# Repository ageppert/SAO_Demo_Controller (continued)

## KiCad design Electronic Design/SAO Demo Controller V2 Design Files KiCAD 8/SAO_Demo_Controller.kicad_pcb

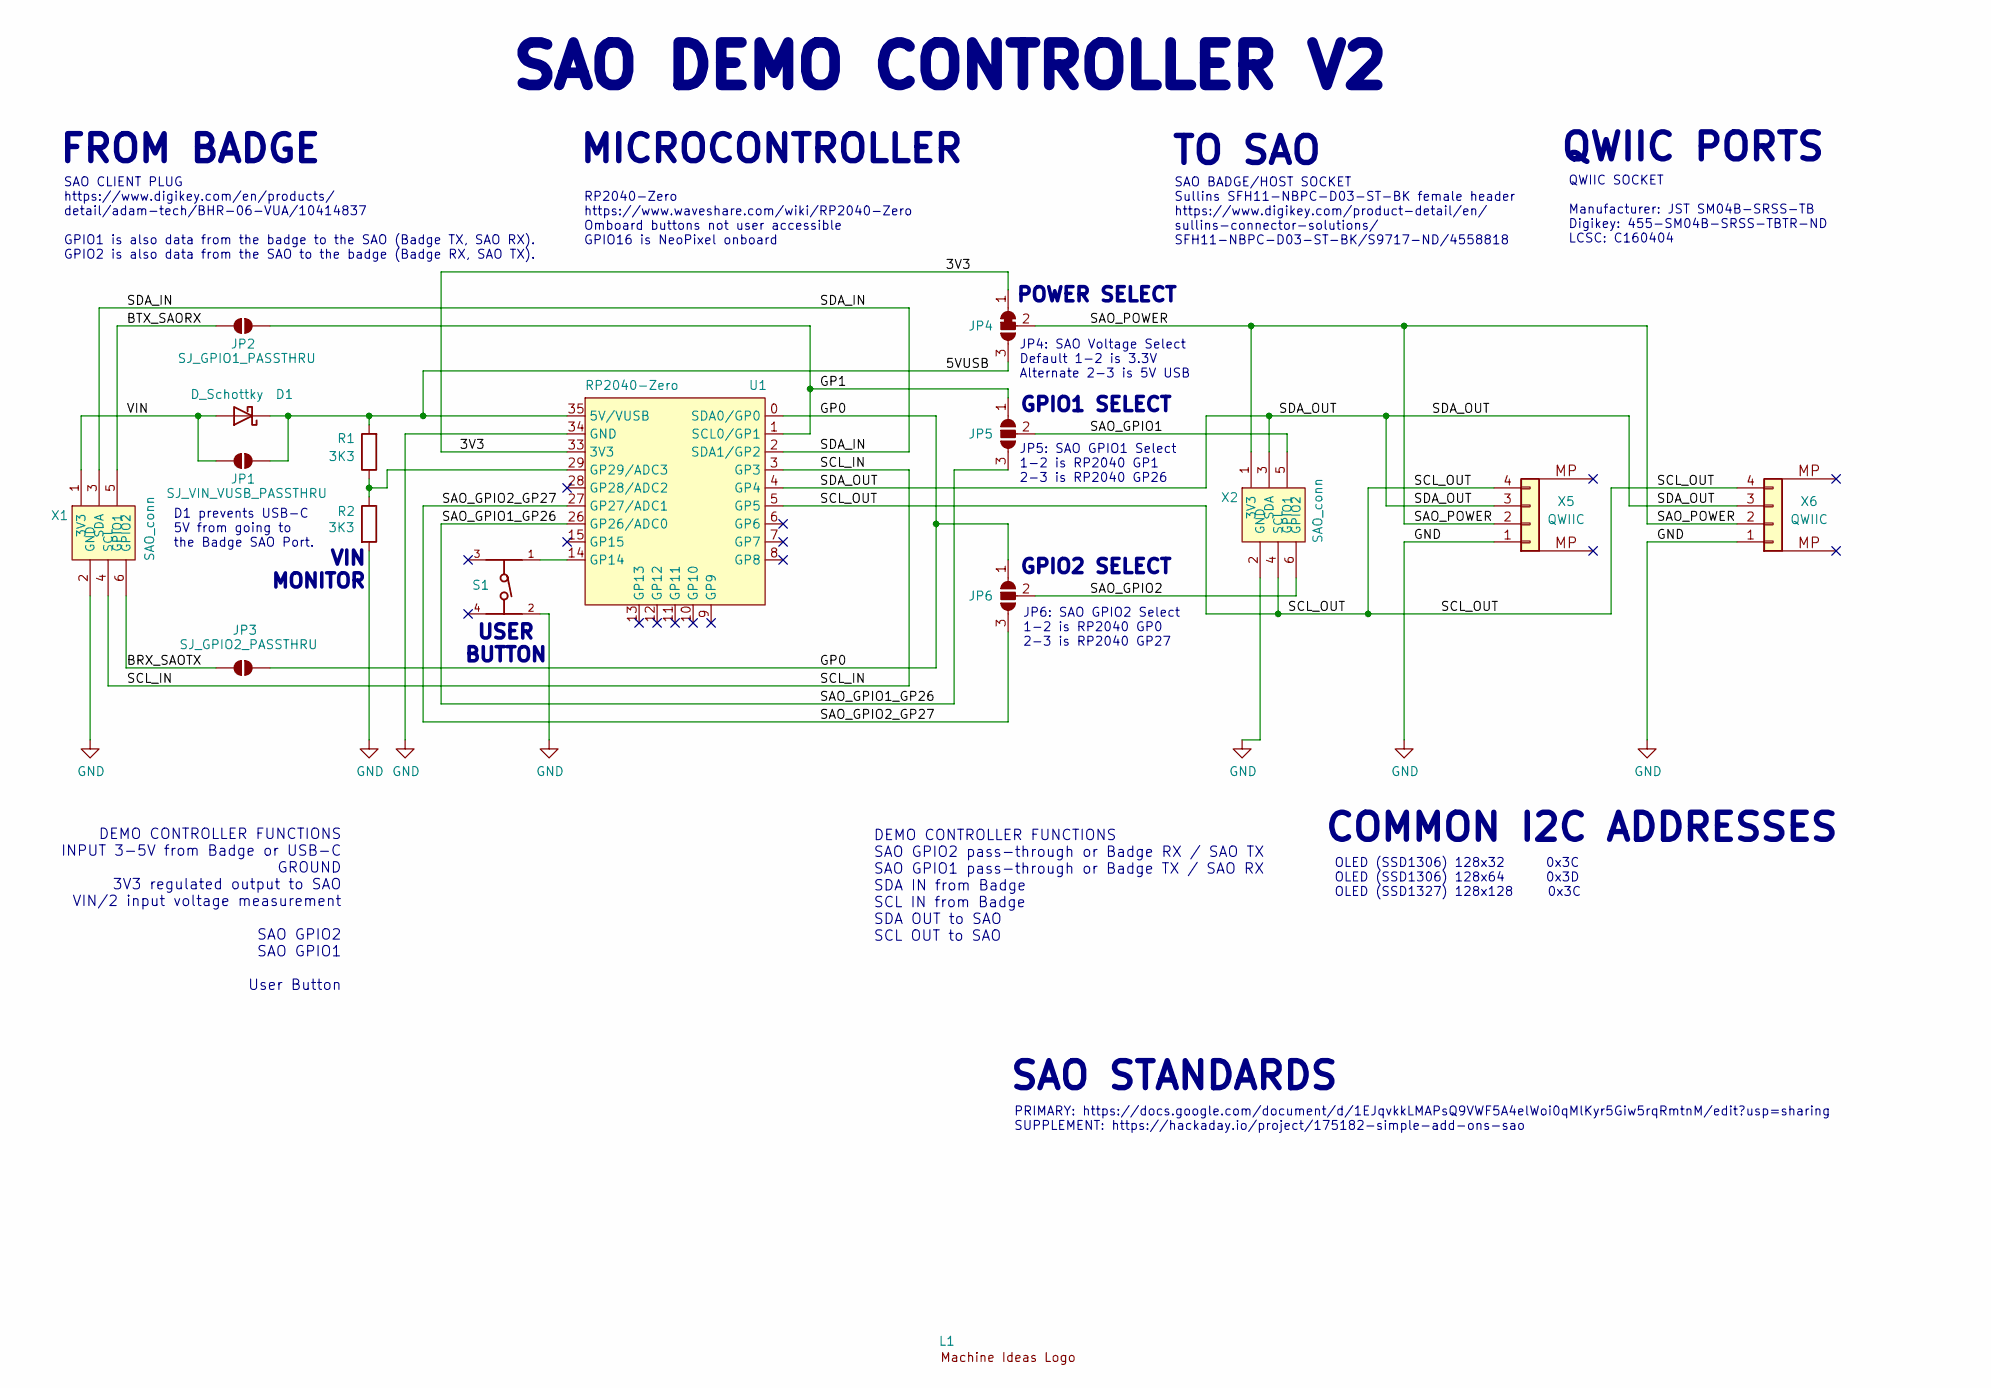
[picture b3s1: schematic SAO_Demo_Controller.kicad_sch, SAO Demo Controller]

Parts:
D1: D_Schottky; D_0805_2012Metric
JP1: SJ_VIN_VUSB_PASSTHRU; SolderJumper-2_P1.3mm_Open_RoundedPad1.0x1.5mm
JP2: SJ_GPIO1_PASSTHRU; SolderJumper-2_P1.3mm_Open_RoundedPad1.0x1.5mm
JP3: SJ_GPIO2_PASSTHRU; SolderJumper-2_P1.3mm_Open_RoundedPad1.0x1.5mm
JP4: SolderJumper_3_Open; SolderJumper-3_P1.3mm_Bridged12_RoundedPad1.0x1.5mm_NumberL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
JP5, JP6: SolderJumper_3_Open; SolderJumper-3_P1.3mm_Open_RoundedPad1.0x1.5mm_NumberLabels
L1: Machine_Ideas_logo
R1, R2: 3K3; R_0805_2012Metric; Manufacturer_Part_Number RK73H2ATTD3301F
S1: 434331045822; Button_Wurth_4343X10458XX; PART-NUMBER 434331045822
U1: RP2040-Zero; RP2040 Zero
X1: SAO_conn; Badgelife-SAOv169-BADGE-2x3-Edge-Connect-no-front-text; MPN SFH11-NBPC-D03-ST-BK
X2: SAO_conn; Badgelife-SAOv169-BADGE-2x3-no-front-text; MPN SFH11-NBPC-D03-ST-BK
X5, X6: QWIIC; JST_SH_SM04B-SRSS-TB_1x04-1MP_P1.00mm_Horizontal; MPN SM04B-SRSS-TB; LCSC C160404

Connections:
/3V3: JP4.1 (A), U1.33 (3V3)
/5VUSB: D1.1 (K), JP1.2 (B), JP4.3 (B), R1.2, U1.35 (5V/VUSB)
/BRX_SAOTX: JP3.1 (A), X1.6 (GPIO2)
/BTX_SAORX: JP2.1 (A), X1.5 (GPIO1)
/GP0: JP3.2 (B), JP6.1 (A), U1.0 (SDA0/GP0)
/GP1: JP2.2 (B), JP5.1 (A), U1.1 (SCL0/GP1)
/SAO_GPIO1: JP5.2 (C), X2.5 (GPIO1)
/SAO_GPIO1_GP26: JP5.3 (B), U1.26 (GP26/ADC0)
/SAO_GPIO2: JP6.2 (C), X2.6 (GPIO2)
/SAO_GPIO2_GP27: JP6.3 (B), U1.27 (GP27/ADC1)
/SAO_POWER: JP4.2 (C), X2.1 (3V3), X5.2, X6.2
/SCL_IN: U1.3 (GP3), X1.4 (SCL)
/SCL_OUT: U1.5 (GP5), X2.4 (SCL), X5.4, X6.4
/SDA_IN: U1.2 (SDA1/GP2), X1.3 (SDA)
/SDA_OUT: U1.4 (GP4), X2.3 (SDA), X5.3, X6.3
/VIN: D1.2 (A), JP1.1 (A), X1.1 (3V3)
GND: R2.2, S1.2, U1.34 (GND), X1.2 (GND), X2.2 (GND), X5.1, X6.1
unnamed: S1.1, U1.14 (GP14)
unnamed: R1.1, R2.1, U1.29 (GP29/ADC3)

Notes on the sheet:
DEMO CONTROLLER FUNCTIONS INPUT 3-5V from Badge or USB-C GROUND 3V3 regulated output to SAO VIN/2 input voltage measurement SAO GPIO2 SAO GPIO1 User Button
POWER SELECT
SAO BADGE/HOST SOCKET Sullins SFH11-NBPC-D03-ST-BK female header https://www.digikey.com/product-detail/en/ sullins-connector-solutions/ SFH11-NBPC-D03-ST-BK/S9717-ND/4558818
COMMON I2C ADDRESSES
QWIIC SOCKET Manufacturer: JST SM04B-SRSS-TB Digikey: 455-SM04B-SRSS-TBTR-ND LCSC: C160404
USER BUTTON
RP2040-Zero https://www.waveshare.com/wiki/RP2040-Zero Omboard buttons not user accessible GPIO16 is NeoPixel onboard
GPIO1 SELECT
DEMO CONTROLLER FUNCTIONS SAO GPIO2 pass-through or Badge RX / SAO TX SAO GPIO1 pass-through or Badge TX / SAO RX SDA IN from Badge SCL IN from Badge SDA OUT to SAO SCL OUT to SAO
SAO CLIENT PLUG https://www.digikey.com/en/products/ detail/adam-tech/BHR-06-VUA/10414837 GPIO1 is also data from the badge to the SAO (Badge TX, SAO RX). GPIO2 is also data from the SAO to the badge (Badge RX, SAO TX).
OLED (SSD1306) 128x32 0x3C OLED (SSD1306) 128x64 0x3D OLED (SSD1327) 128x128 0x3C
FROM BADGE
SAO STANDARDS
JP4: SAO Voltage Select Default 1-2 is 3.3V Alternate 2-3 is 5V USB
PRIMARY: https://docs.google.com/document/d/1EJqvkkLMAPsQ9VWF5A4elWoi0qMlKyr5Giw5rqRmtnM/edit?usp=sharing SUPPLEMENT: https://hackaday.io/project/175182-simple-add-ons-sao
VIN MONITOR
QWIIC PORTS
JP5: SAO GPIO1 Select 1-2 is RP2040 GP1 2-3 is RP2040 GP26
TO SAO
D1 prevents USB-C 5V from going to the Badge SAO Port.
JP6: SAO GPIO2 Select 1-2 is RP2040 GP0 2-3 is RP2040 GP27
SAO DEMO CONTROLLER V2
GPIO2 SELECT
MICROCONTROLLER

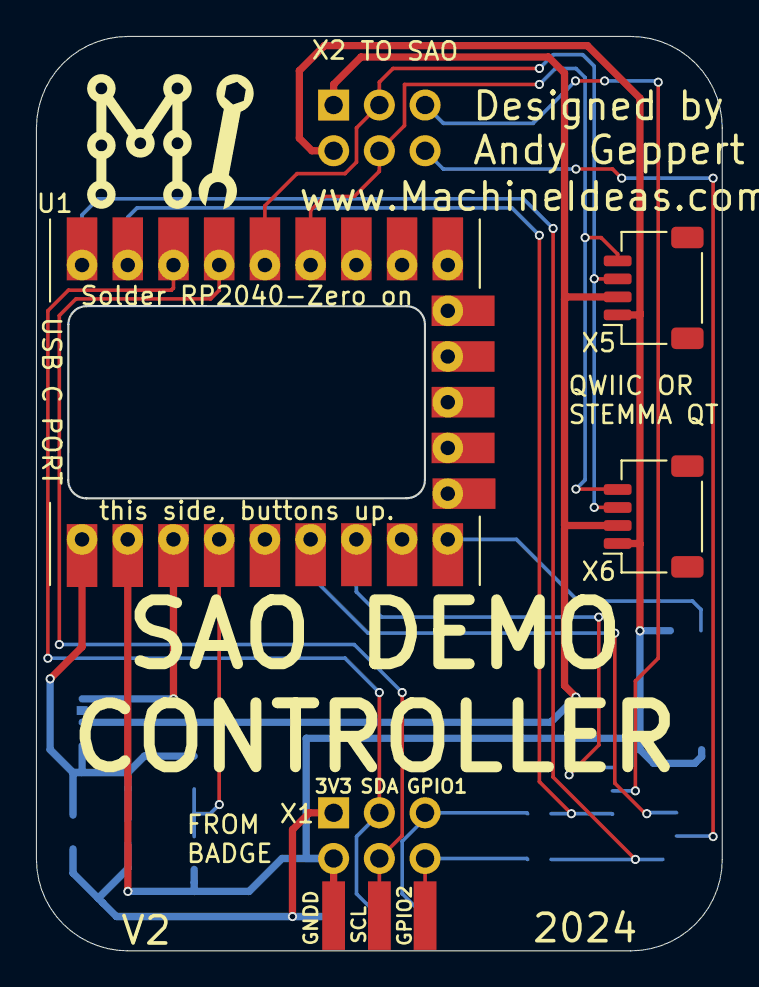
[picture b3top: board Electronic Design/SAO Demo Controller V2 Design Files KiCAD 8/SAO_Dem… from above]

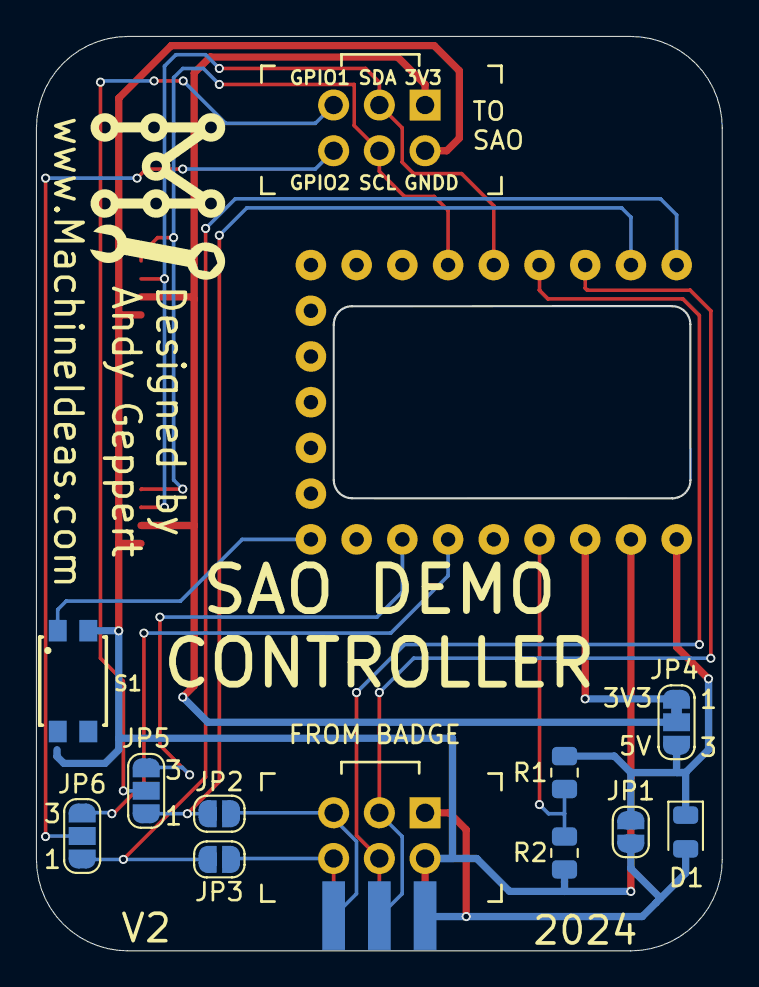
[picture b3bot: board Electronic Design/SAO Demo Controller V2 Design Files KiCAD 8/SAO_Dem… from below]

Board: 2 copper layers, 38.0 x 50.7 mm, 17 parts (11 on the bottom side), 19 nets.

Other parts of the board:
L1#2: Machine_Ideas_logo

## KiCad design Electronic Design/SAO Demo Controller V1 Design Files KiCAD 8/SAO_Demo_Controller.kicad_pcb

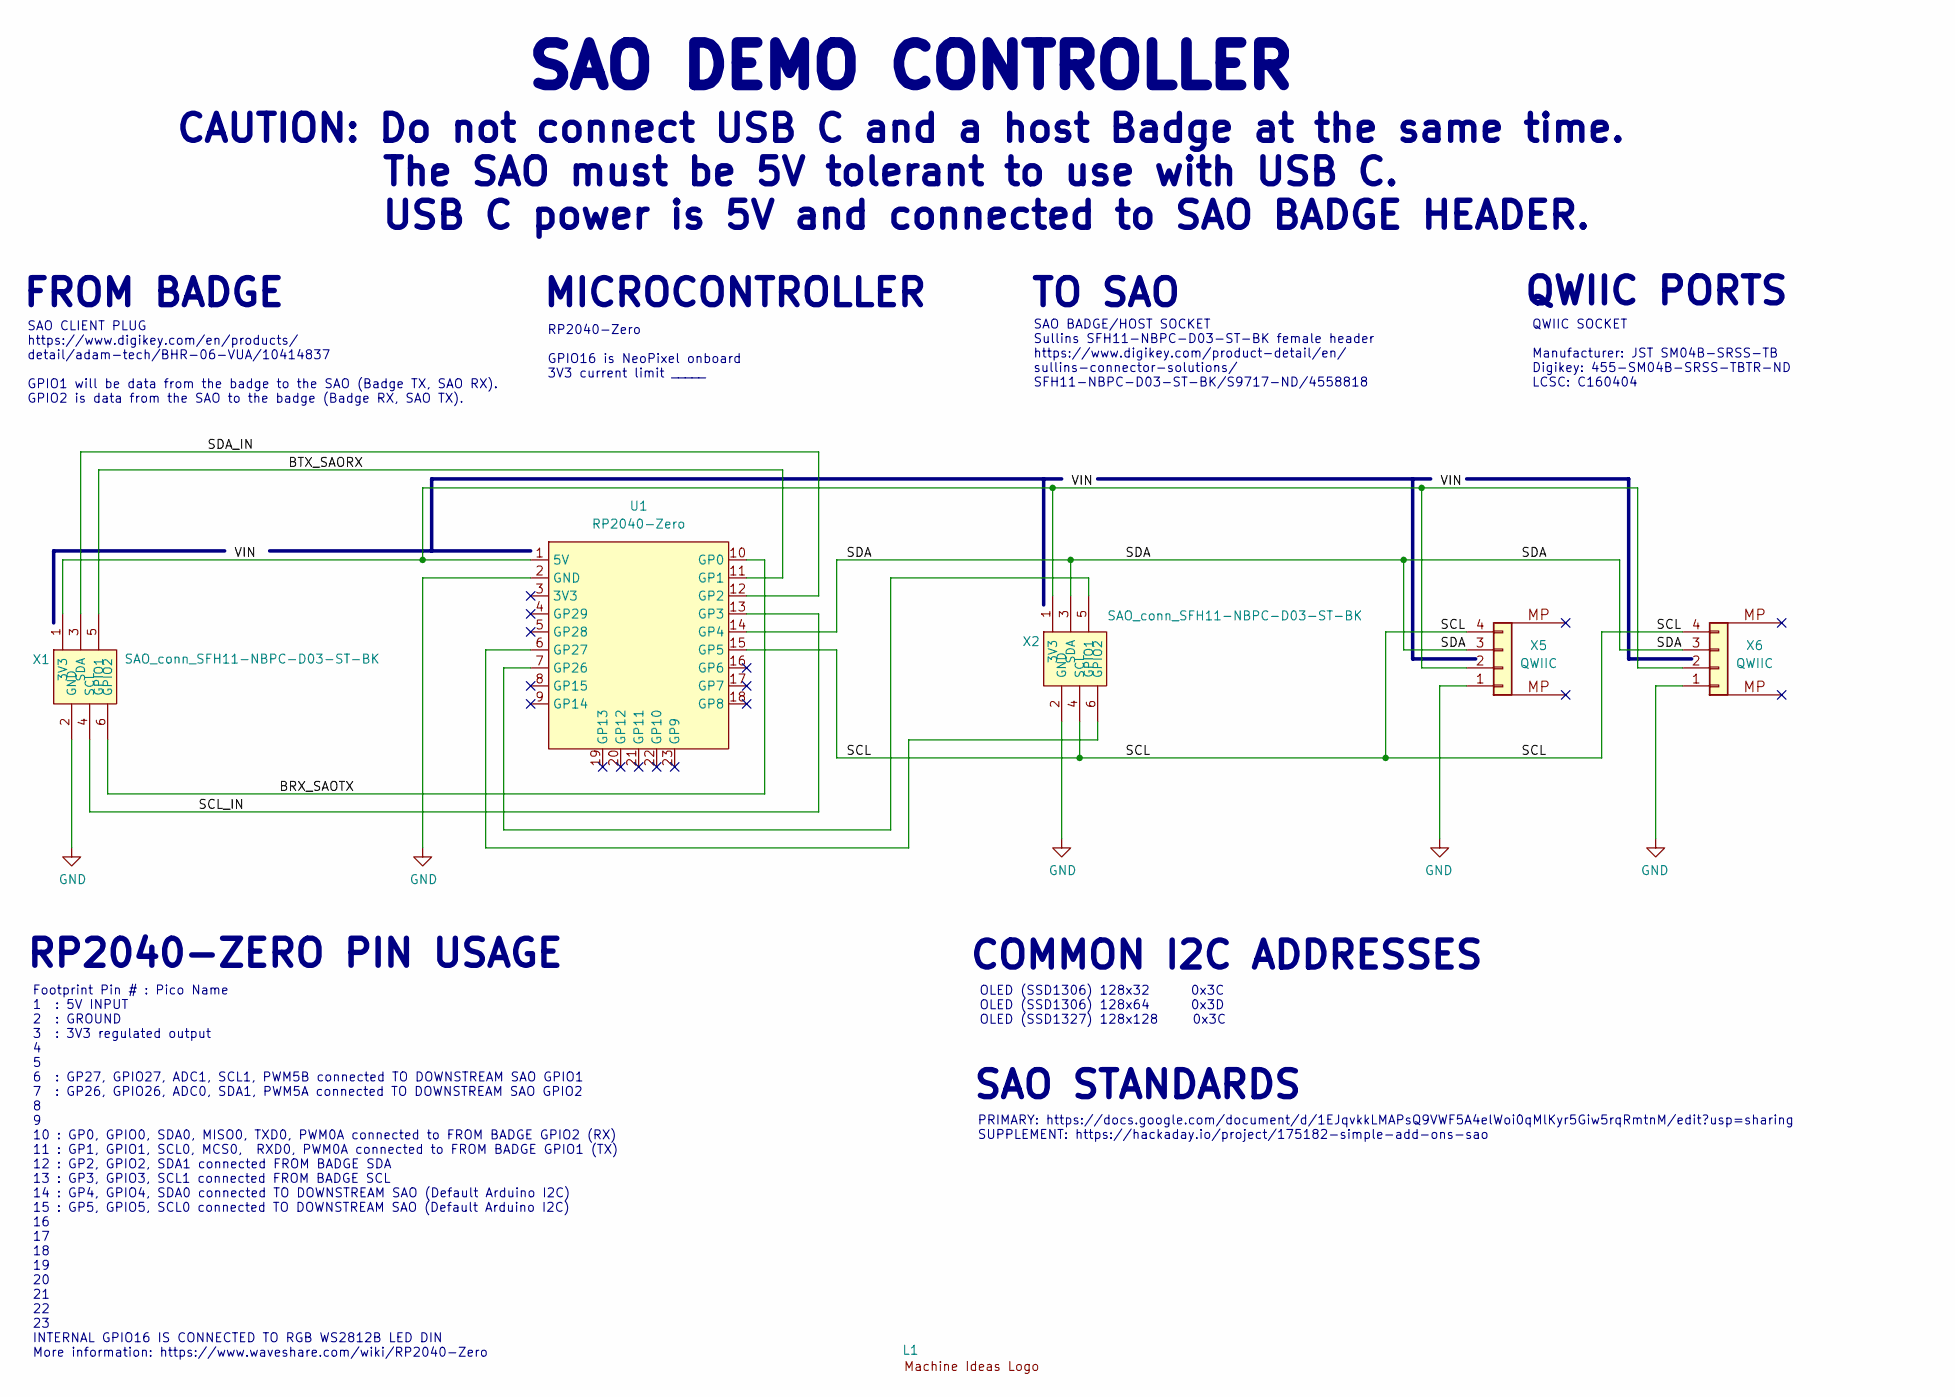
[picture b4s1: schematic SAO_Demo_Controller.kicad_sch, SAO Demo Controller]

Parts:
L1: Machine_Ideas_logo
U1: RP2040-Zero; RP2040 Zero
X1: SAO_conn_SFH11-NBPC-D03-ST-BK; Badgelife-SAOv169-BADGE-2x3-Edge-Connect-no-front-text; MPN SFH11-NBPC-D03-ST-BK
X2: SAO_conn_SFH11-NBPC-D03-ST-BK; Badgelife-SAOv169-BADGE-2x3-no-front-text; MPN SFH11-NBPC-D03-ST-BK
X5, X6: QWIIC; JST_SH_SM04B-SRSS-TB_1x04-1MP_P1.00mm_Horizontal; MPN SM04B-SRSS-TB; LCSC C160404

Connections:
/BRX_SAOTX: U1.10 (GP0), X1.6 (GPIO2)
/BTX_SAORX: U1.11 (GP1), X1.5 (GPIO1)
/SCL: U1.15 (GP5), X2.4 (SCL), X5.4, X6.4
/SCL_IN: U1.13 (GP3), X1.4 (SCL)
/SDA: U1.14 (GP4), X2.3 (SDA), X5.3, X6.3
/SDA_IN: U1.12 (GP2), X1.3 (SDA)
/VIN: U1.1 (5V), X1.1 (3V3), X2.1 (3V3), X5.2, X6.2
GND: U1.2 (GND), X1.2 (GND), X2.2 (GND), X5.1, X6.1
unnamed: U1.7 (GP26), X2.5 (GPIO1)
unnamed: U1.6 (GP27), X2.6 (GPIO2)

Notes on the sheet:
SAO BADGE/HOST SOCKET Sullins SFH11-NBPC-D03-ST-BK female header https://www.digikey.com/product-detail/en/ sullins-connector-solutions/ SFH11-NBPC-D03-ST-BK/S9717-ND/4558818
COMMON I2C ADDRESSES
QWIIC SOCKET Manufacturer: JST SM04B-SRSS-TB Digikey: 455-SM04B-SRSS-TBTR-ND LCSC: C160404
RP2040-Zero GPIO16 is NeoPixel onboard 3V3 current limit _____
RP2040-ZERO PIN USAGE
Footprint Pin # : Pico Name 1 : 5V INPUT 2 : GROUND 3 : 3V3 regulated output 4 5 6 : GP27, GPIO27, ADC1, SCL1, PWM5B connected TO DOWNSTREAM SAO GPIO1 7 : GP26, GPIO26, ADC0, SDA1, PWM5A connected TO DOWNSTREAM SAO GPIO2 8 9 10 : GP0, GPIO0, SDA0, MISO0, TXD0, PWM0A connected to FROM BADGE GPIO2 (R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
SAO CLIENT PLUG https://www.digikey.com/en/products/ detail/adam-tech/BHR-06-VUA/10414837 GPIO1 will be data from the badge to the SAO (Badge TX, SAO RX). GPIO2 is data from the SAO to the badge (Badge RX, SAO TX).
OLED (SSD1306) 128x32 0x3C OLED (SSD1306) 128x64 0x3D OLED (SSD1327) 128x128 0x3C
FROM BADGE
SAO STANDARDS
PRIMARY: https://docs.google.com/document/d/1EJqvkkLMAPsQ9VWF5A4elWoi0qMlKyr5Giw5rqRmtnM/edit?usp=sharing SUPPLEMENT: https://hackaday.io/project/175182-simple-add-ons-sao
QWIIC PORTS
TO SAO
CAUTION: Do not connect USB C and a host Badge at the same time. The SAO must be 5V tolerant to use with USB C. USB C power is 5V and connected to SAO BADGE HEADER.
SAO DEMO CONTROLLER
MICROCONTROLLER

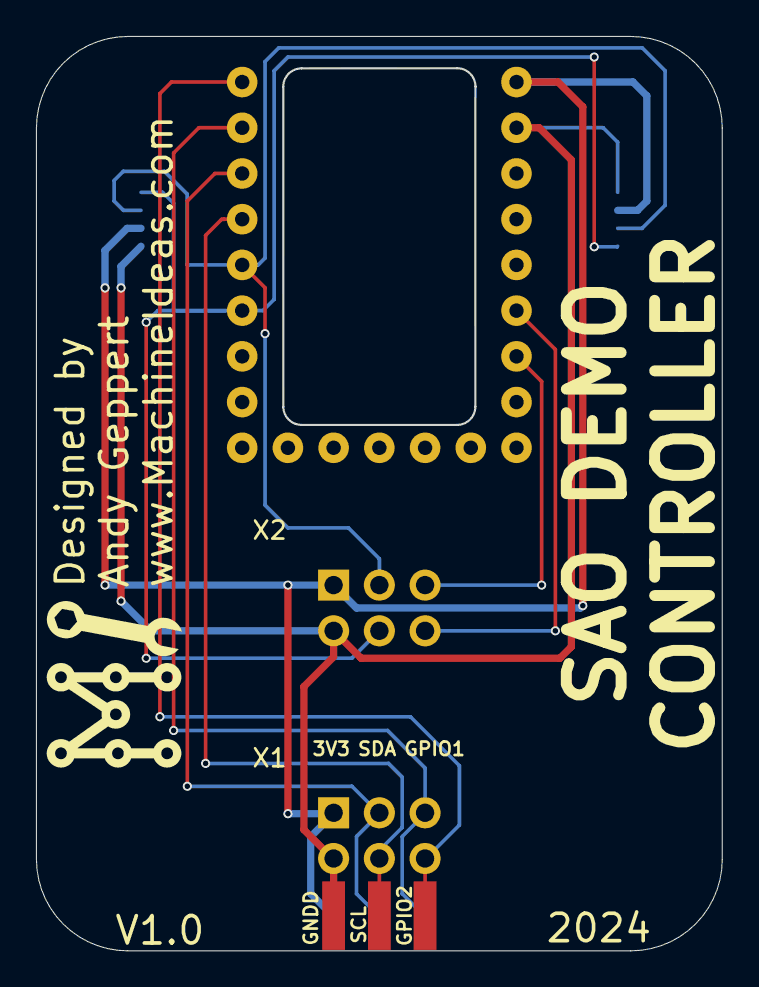
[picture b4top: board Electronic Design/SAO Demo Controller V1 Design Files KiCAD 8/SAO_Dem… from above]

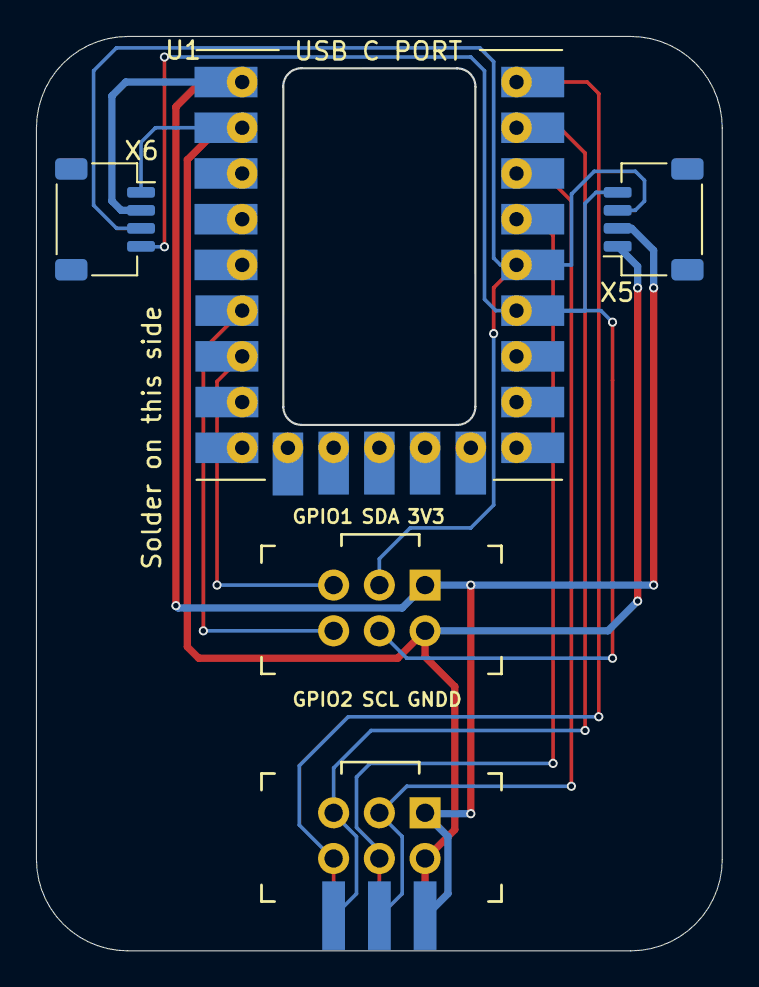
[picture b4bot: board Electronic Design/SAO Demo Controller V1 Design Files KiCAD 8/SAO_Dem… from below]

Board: 2 copper layers, 38.0 x 50.7 mm, 6 parts (3 on the bottom side), 10 nets.

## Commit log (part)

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2024-10-04 Add Demo Firmware for OLED SSD1306 128x32
2024-10-04 Add Demo Firmware for built-in RGB LED
2024-10-10 Rename schematic V1.0
2024-10-14 Begin V2 design improvements
2024-10-29 Update V2 schematics, docs, renders
2024-11-16 Create DEMO_CONTROLLER_TEST.ino
    Expanding test features for all built-in functionality
